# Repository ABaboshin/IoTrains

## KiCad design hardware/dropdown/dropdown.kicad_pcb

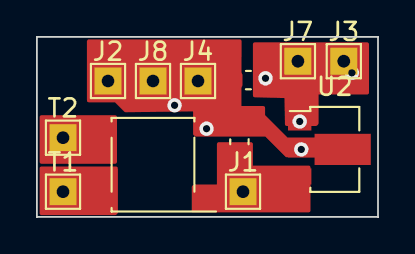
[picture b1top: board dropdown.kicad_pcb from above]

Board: 2 copper layers, 19.0 x 10.0 mm, 12 parts (0 on the bottom side), 5 nets.

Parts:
C1, C2: 10uF; C_0603_1608Metric
D3: ABS2; Diode_Bridge_Diotec_ABS
J1: 12; TestPoint_THTPad_1.5x1.5mm_Drill0.7mm
J2, J4, J8: G; TestPoint_THTPad_1.5x1.5mm_Drill0.7mm
J3, J7: 3; TestPoint_THTPad_1.5x1.5mm_Drill0.7mm
T1: T1; TestPoint_THTPad_1.5x1.5mm_Drill0.7mm
T2: T2; TestPoint_THTPad_1.5x1.5mm_Drill0.7mm
U2: AMS1117-3.3; SOT-89-3

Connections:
+3.3V: C1.1, J3.1, J7.1, U2.1 (VO)
+12V: D3.4, T1.1
GND: C1.2, C2.2, D3.2 (-), J2.1, J4.1, J8.1, U2.2 (GND)
GND1: D3.3, T2.1
VD: C2.1, D3.1 (+), J1.1, U2.3 (VI)

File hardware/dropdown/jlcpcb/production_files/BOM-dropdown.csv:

Comment,Designator,Footprint,LCSC
AMS1117-3.3,U2,SOT-89-3,C347256
T2,T2,TestPoint_THTPad_1.5x1.5mm_Drill0.7mm,
T1,T1,TestPoint_THTPad_1.5x1.5mm_Drill0.7mm,
G,J4,TestPoint_THTPad_1.5x1.5mm_Drill0.7mm,
3,J3,TestPoint_THTPad_1.5x1.5mm_Drill0.7mm,
G,J2,TestPoint_THTPad_1.5x1.5mm_Drill0.7mm,
12,J1,TestPoint_THTPad_1.5x1.5mm_Drill0.7mm,
10uF,C2,C_0603_1608Metric,
ABS2,D3,Diode_Bridge_Diotec_ABS,
10uF,C1,C_0603_1608Metric,
G,J8,TestPoint_THTPad_1.5x1.5mm_Drill0.7mm,
3,J7,TestPoint_THTPad_1.5x1.5mm_Drill0.7mm,
